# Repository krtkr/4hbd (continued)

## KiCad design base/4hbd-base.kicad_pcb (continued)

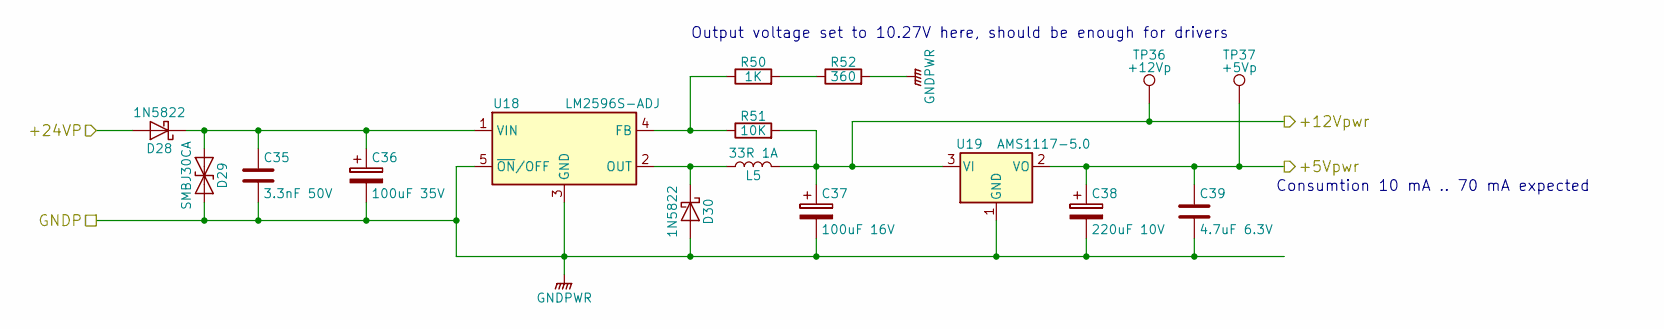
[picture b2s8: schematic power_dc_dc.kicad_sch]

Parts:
C35: 3.3nF 50V; C_0603_1608Metric
C36: 100uF 35V; CP_Elec_6.3x7.7
C37: 100uF 16V; CP_Elec_6.3x5.3
C38: 220uF 10V; CP_Elec_6.3x5.3
C39: 4.7uF 6.3V; C_0603_1608Metric
D28, D30: 1N5822; D_SMA
D29: SMBJ30CA; D_SMB
L5: 33R 1A; L_7.3x7.3_H3.5
R50: 1K; R_0603_1608Metric
R51: 10K; R_0603_1608Metric
R52: 360; R_0603_1608Metric
TP36: +12Vp; TestPoint_Pad_D1.5mm
TP37: +5Vp; TestPoint_Pad_D1.5mm
U18: LM2596S-ADJ; TO-263-5_TabPin3
U19: AMS1117-5.0; SOT-223

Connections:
/DIO/+12V: C37.1, L5.2, R51.2, TP36.1, U19.3 (VI); also elsewhere on the board
/MOSFETs/CurSense/Isolation/+5Vpwr: C38.1, C39.1, TP37.1, U19.2 (VO), U19.4; also elsewhere on the board
/Power DC/DC/+24VP: D28.2 (A); also elsewhere on the board
GNDPWR: C35.2, C36.2, C37.2, C38.2, C39.2, D29.2 (A2), D30.2 (A), R52.2, U18.3 (GND), U18.5 (~ON/OFF), U19.1 (GND); also elsewhere on the board
unnamed: C35.1, C36.1, D28.1 (K), D29.1 (A1), U18.1 (VIN)
unnamed: D30.1 (K), L5.1, U18.2 (OUT)
unnamed: R50.1, R51.1, U18.4 (FB)
unnamed: R50.2, R52.1

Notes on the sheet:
Output voltage set to 10.27V here, should be enough for drivers
Consumtion 10 mA .. 70 mA expected

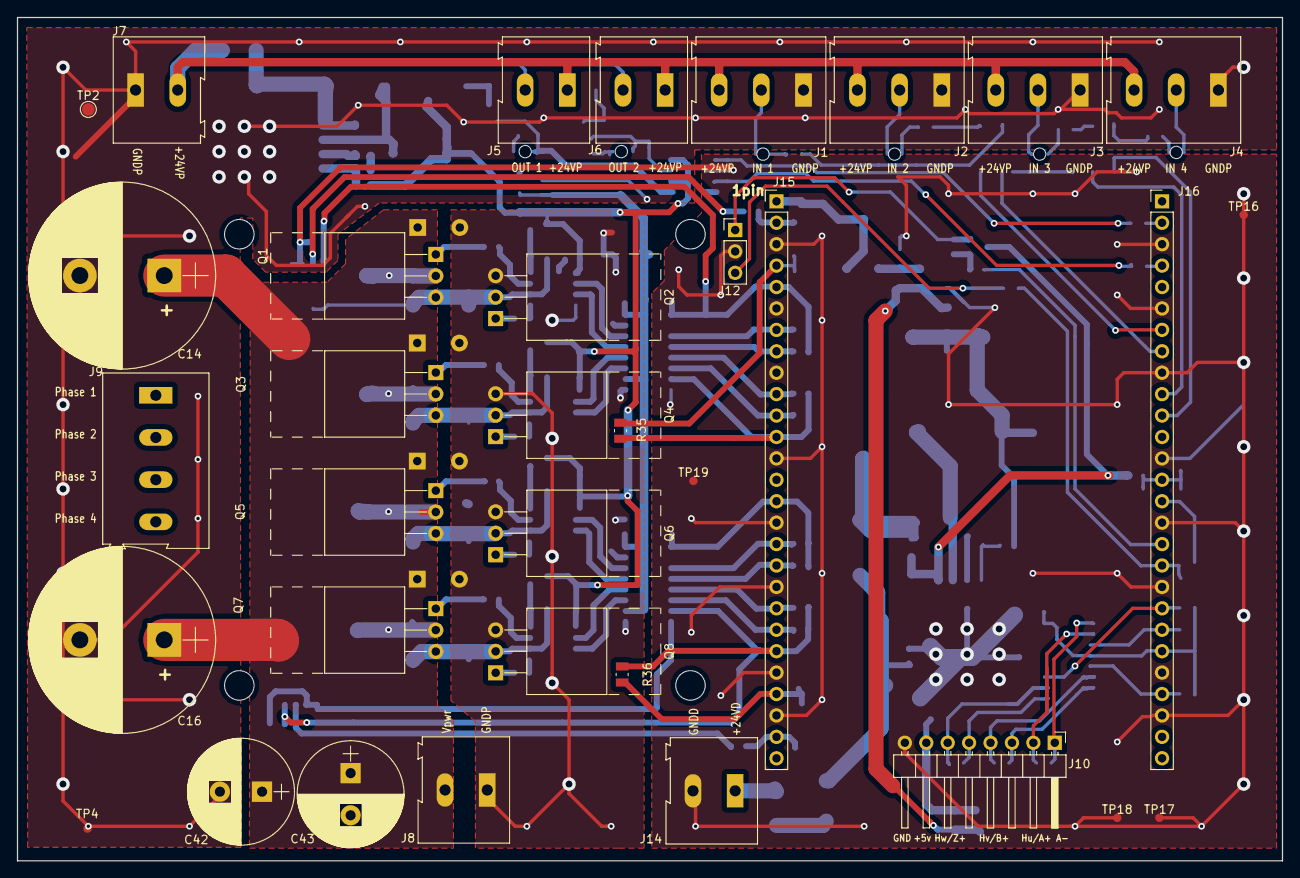
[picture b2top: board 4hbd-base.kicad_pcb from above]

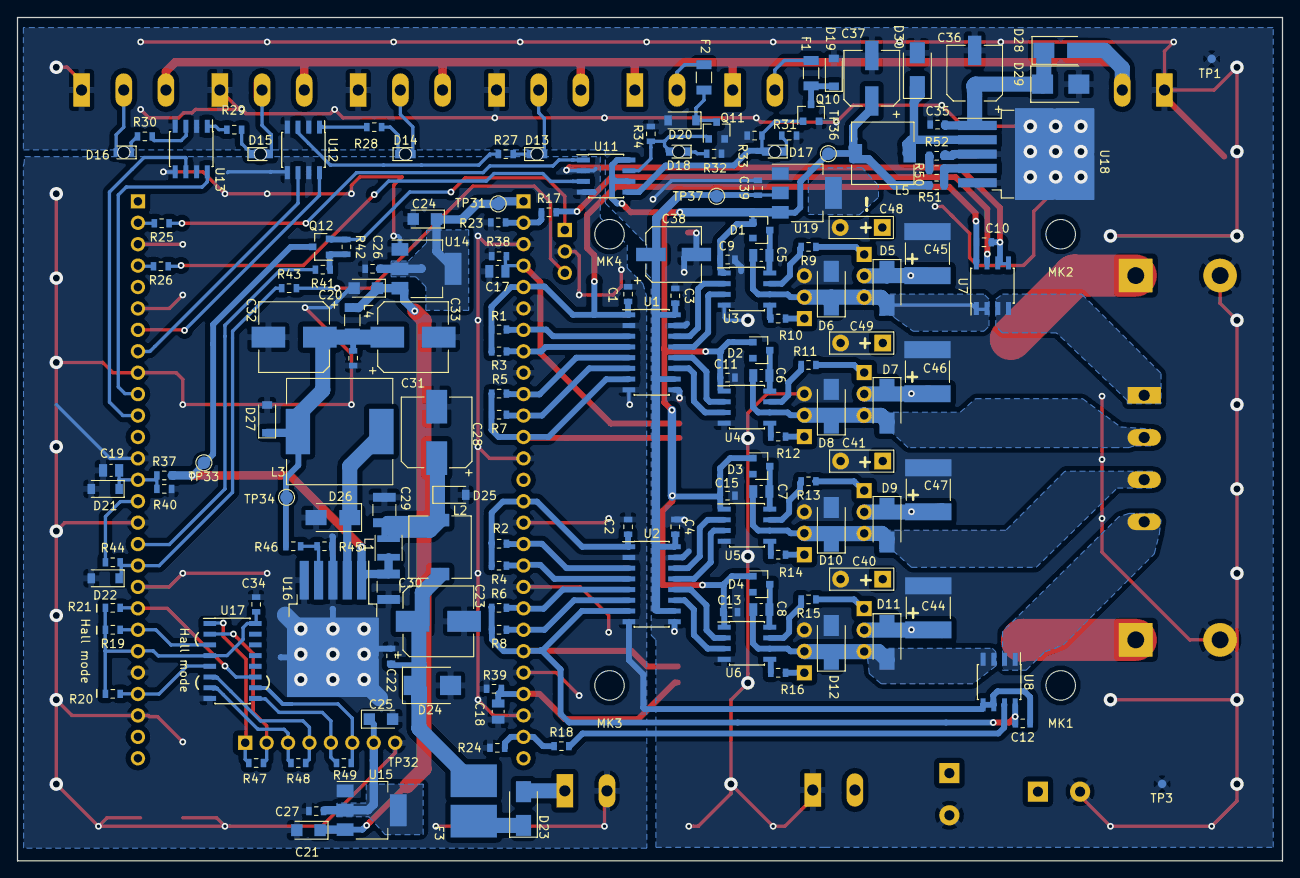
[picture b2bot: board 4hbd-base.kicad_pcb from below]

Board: 2 copper layers, 150.0 x 100.0 mm, 198 parts (164 on the bottom side), 113 nets.

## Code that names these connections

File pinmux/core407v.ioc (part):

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Mcu.Name=STM32F407V(E-G)Tx
Mcu.Package=LQFP100
Mcu.UserName=STM32F407VETx
PA0-WKUP.GPIOParameters=GPIO_Label
PA0-WKUP.GPIO_Label=ENC_A
PA0-WKUP.Signal=S_TIM2_CH1_ETR
PA1.GPIOParameters=GPIO_Label
PA1.GPIO_Label=ENC_B
PA1.Signal=S_TIM2_CH2
PA10.Mode=OTG/Dual_Role_Device
PA10.Signal=USB_OTG_FS_ID
PA11.Mode=OTG/Dual_Role_Device
PA11.Signal=USB_OTG_FS_DM
PA12.Mode=OTG/Dual_Role_Device
PA12.Signal=USB_OTG_FS_DP
PA13.Mode=JTAG_5_pins
PA13.Signal=SYS_JTMS-SWDIO
PA14.Mode=JTAG_5_pins
PA14.Signal=SYS_JTCK-SWCLK
PA15.Mode=JTAG_5_pins
PA15.Signal=SYS_JTDI
PA2.GPIOParameters=GPIO_Label
PA2.GPIO_Label=ENC_Z
PA2.Signal=GPIO_Input
PA4.Mode=NSS_Signal_Hard_Output
PA4.Signal=SPI1_NSS
PA5.Mode=Full_Duplex_Master
PA5.Signal=SPI1_SCK
PA6.Mode=Full_Duplex_Master
PA6.Signal=SPI1_MISO
PA7.Mode=Full_Duplex_Master
PA7.Signal=SPI1_MOSI
PA8.Mode=Activate_SOF_FS
PA8.Signal=USB_OTG_FS_SOF
PA9.Mode=Activate_VBUS
PA9.Signal=USB_OTG_FS_VBUS
PB1.Signal=ADCx_IN9
PB12.Mode=NSS_Signal_Hard_Output
PB12.Signal=SPI2_NSS
PB13.Mode=Full_Duplex_Master
PB13.Signal=SPI2_SCK
PB14.Mode=Full_Duplex_Master
PB14.Signal=SPI2_MISO
PB15.Mode=Full_Duplex_Master
PB15.Signal=SPI2_MOSI
PB3.Mode=JTAG_5_pins
PB3.Signal=SYS_JTDO-SWO
PB4.Mode=JTAG_5_pins
PB4.Signal=SYS_JTRST
PB5.GPIOParameters=GPIO_Label
PB5.GPIO_Label=USART1_DE
PB5.Signal=GPIO_Output
PB6.Mode=Asynchronous
PB6.Signal=USART1_TX
PB7.Mode=Asynchronous
PB7.Signal=USART1_RX
PB8.Mode=Master
PB8.Signal=CAN1_RX
PB9.Mode=Master
PB9.Signal=CAN1_TX
PC0.Signal=ADCx_IN10
PC14-OSC32_IN.Mode=LSE-External-Oscillator
PC14-OSC32_IN.Signal=RCC_OSC32_IN
PC15-OSC32_OUT.Mode=LSE-External-Oscillator
PC15-OSC32_OUT.Signal=RCC_OSC32_OUT
PC2.Signal=ADCx_IN12
PC4.Signal=ADCx_IN14
PC5.Signal=ADCx_IN15
PC6.GPIOParameters=GPIO_Label
PC6.GPIO_Label=FAN_PWM
PC6.Signal=S_TIM3_CH1
PD0.GPIOParameters=GPIO_Label
PD0.GPIO_Label=DI0
PD0.Signal=GPIO_Input
PD1.GPIOParameters=GPIO_Label
PD1.GPIO_Label=DI1
PD1.Signal=GPIO_Input
PD12.GPIOParameters=GPIO_Label
PD12.GPIO_Label=FAN_Pulse
PD12.Signal=S_TIM4_CH1
PD2.GPIOParameters=GPIO_Label
PD2.GPIO_Label=DI2
PD2.Signal=GPIO_Input
PD3.GPIOParameters=GPIO_Label
PD3.GPIO_Label=DI3
PD3.Signal=GPIO_Input
PD4.GPIOParameters=GPIO_Label
PD4.GPIO_Label=DO0
PD4.Signal=GPIO_Output
PD5.GPIOParameters=GPIO_Label
PD5.GPIO_Label=DO1
PD5.Signal=GPIO_Output
PE10.GPIOParameters=GPIO_Label
PE10.GPIO_Label=PWM1n
PE10.Mode=PWM Generation2 CH2 CH2N
PE10.Signal=TIM1_CH2N
PE11.GPIOParameters=GPIO_Label
PE11.GPIO_Label=PWM1p
PE11.Signal=S_TIM1_CH2
PE12.GPIOParameters=GPIO_Label
PE12.GPIO_Label=PWM2n
PE12.Mode=PWM Generation3 CH3 CH3N
PE12.Signal=TIM1_CH3N
PE13.GPIOParameters=GPIO_Label
PE13.GPIO_Label=PWM2p
PE13.Signal=S_TIM1_CH3
PE14.GPIOParameters=GPIO_Label
PE14.GPIO_Label=PWM3p
PE14.Signal=S_TIM1_CH4
PE15.GPIOParameters=GPIO_Label
PE15.GPIO_Label=PWM_Trip
PE15.Mode=Activate-Break-Input
PE15.Signal=TIM1_BKIN
PE7.GPIOParameters=GPIO_Label
PE7.GPIO_Label=PWM3n
PE7.Signal=GPIO_Output
PE8.GPIOParameters=GPIO_Label
PE8.GPIO_Label=PWM0n
PE8.Mode=PWM Generation1 CH1 CH1N
PE8.Signal=TIM1_CH1N
PE9.GPIOParameters=GPIO_Label
PE9.GPIO_Label=PWM0p
PE9.Signal=S_TIM1_CH1
PH0-OSC_IN.Mode=HSE-External-Oscillator
PH0-OSC_IN.Signal=RCC_OSC_IN
PH1-OSC_OUT.Mode=HSE-External-Oscillator
PH1-OSC_OUT.Signal=RCC_OSC_OUT
RCC.HSE_VALUE=8000000
RCC.SYSCLKFreq_VALUE=168000000
RCC.SYSCLKSource=RCC_SYSCLKSOURCE_PLLCLK

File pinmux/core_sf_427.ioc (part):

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Mcu.Name=STM32F427V(G-I)Tx
Mcu.Package=LQFP100
Mcu.UserName=STM32F427VGTx
PA0/WKUP.Signal=ADCx_IN0
PA1.Mode=RMII
PA1.Signal=ETH_REF_CLK
PA10.Signal=S_TIM1_CH3
PA11.Signal=S_TIM1_CH4
PA13.Mode=JTAG_5_pins
PA13.Signal=SYS_JTMS-SWDIO
PA14.Mode=JTAG_5_pins
PA14.Signal=SYS_JTCK-SWCLK
PA15.Mode=JTAG_5_pins
PA15.Signal=SYS_JTDI
PA2.Mode=RMII
PA2.Signal=ETH_MDIO
PA3.Signal=ADCx_IN3
PA4.Signal=ADCx_IN4
PA5.GPIOParameters=GPIO_Label
PA5.GPIO_Label=TIM1_CH2N
PA5.Signal=GPIO_Output
PA6.Mode=Activate-Break-Input
PA6.Signal=TIM1_BKIN
PA7.Mode=RMII
PA7.Signal=ETH_CRS_DV
PA8.Signal=S_TIM1_CH1
PA9.Signal=S_TIM1_CH2
PB0.GPIOParameters=GPIO_Label
PB0.GPIO_Label=TIM3_FAN_PWM
PB0.Signal=S_TIM3_CH3
PB1.Signal=ADCx_IN9
PB10.GPIOParameters=GPIO_Label
PB10.GPIO_Label=TIM2_FAN_PULSE
PB10.Signal=S_TIM2_CH3
PB11.Mode=RMII
PB11.Signal=ETH_TX_EN
PB12.Mode=RMII
PB12.Signal=ETH_TXD0
PB13.Mode=RMII
PB13.Signal=ETH_TXD1
PB14.GPIOParameters=GPIO_Label
PB14.GPIO_Label=USART3_DE
PB14.Signal=GPIO_Output
PB2/BOOT1.GPIOParameters=GPIO_Label
PB2/BOOT1.GPIO_Label=TIM1_CH1N
PB2/BOOT1.Signal=GPIO_Output
PB3.Mode=JTAG_5_pins
PB3.Signal=SYS_JTDO-SWO
PB4.Mode=JTAG_5_pins
PB4.Signal=SYS_JTRST
PB7.Signal=FMC_NL
PB8.Mode=Master
PB8.Signal=CAN1_RX
PB9.Mode=Master
PB9.Signal=CAN1_TX
PC0.Signal=ADCx_IN10
PC1.Mode=RMII
PC1.Signal=ETH_MDC
PC10.Mode=Asynchronous
PC10.Signal=USART3_TX
PC11.Mode=Asynchronous
PC11.Signal=USART3_RX
PC2.GPIOParameters=GPIO_Label
PC2.GPIO_Label=TIM1_CH4N
PC2.Signal=GPIO_Output
PC3.GPIOParameters=GPIO_Label
PC3.GPIO_Label=TIM1_CH3N
PC3.Signal=GPIO_Output
PC4.Mode=RMII
PC4.Signal=ETH_RXD0
PC5.Mode=RMII
PC5.Signal=ETH_RXD1
PD0.Mode=16b-da1
PD0.Signal=FMC_DA2
PD1.Mode=16b-da1
PD1.Signal=FMC_DA3
PD10.Mode=16b-da1
PD10.Signal=FMC_DA15
PD11.GPIOParameters=GPIO_Label
PD11.GPIO_Label=TIM4_ENC_Z
PD11.Signal=GPIO_Input
PD12.GPIOParameters=GPIO_Label
PD12.GPIO_Label=TIM4_ENC_A
PD12.Signal=S_TIM4_CH1
PD13.GPIOParameters=GPIO_Label
PD13.GPIO_Label=TIM4_ENC_B
PD13.Signal=S_TIM4_CH2
PD14.Mode=16b-da1
PD14.Signal=FMC_DA0
PD15.Mode=16b-da1
PD15.Signal=FMC_DA1
PD3.Mode=BurstReadWrite1
PD3.Signal=FMC_CLK
PD4.Mode=MuxedPsram1
PD4.Signal=FMC_NOE
PD5.Mode=MuxedPsram1
PD5.Signal=FMC_NWE
PD6.Mode=SynchronousWait1
PD6.Signal=FMC_NWAIT
PD7.Mode=NorPsramChipSelect1_1
PD7.Signal=FMC_NE1
PD8.Mode=16b-da1
PD8.Signal=FMC_DA13
PD9.Mode=16b-da1
PD9.Signal=FMC_DA14
PE0.Mode=2ByteEnable1
PE0.Signal=FMC_NBL0
PE1.Mode=2ByteEnable1
PE1.Signal=FMC_NBL1
PE10.Mode=16b-da1
PE10.Signal=FMC_DA7
PE11.Mode=16b-da1
PE11.Signal=FMC_DA8
PE12.Mode=16b-da1
PE12.Signal=FMC_DA9
PE13.Mode=16b-da1
PE13.Signal=FMC_DA10
PE14.Mode=16b-da1
PE14.Signal=FMC_DA11
PE15.Mode=16b-da1
PE15.Signal=FMC_DA12
PE7.Mode=16b-da1
PE7.Signal=FMC_DA4
PE8.Mode=16b-da1
PE8.Signal=FMC_DA5
PE9.Mode=16b-da1
PE9.Signal=FMC_DA6
PH0/OSC_IN.Mode=HSE-External-Clock-Source
PH0/OSC_IN.Signal=RCC_OSC_IN
PH1/OSC_OUT.Mode=HSE-External-Clock-Source
PH1/OSC_OUT.Signal=RCC_OSC_OUT
RCC.HSE_VALUE=8000000
RCC.SYSCLKFreq_VALUE=180000000
RCC.SYSCLKSource=RCC_SYSCLKSOURCE_PLLCLK

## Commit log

2017-11-27 Initial hierarchy of 4hbd base board.
2017-11-27 Two transistors was added to mosfets_sens_isol.sch
2017-11-28 1. krtkr/kicad-library was included
    2. mosfets_sens_isol.sch was edited
2017-11-29 Change path for lib krtkr/kicad-library
2017-11-29 fix 'R'
2017-11-29 1. Use submodules to track kicad-library used with project. 2. Use relative path for library search path.
2017-12-02 draft 0.01 of mosfets_sens_isol.sch
2017-12-04 draft 0.02 of mosfets_sens_isol.sch
2017-12-08 Add recent kicad footprints into repository.
2017-12-08 1. Update footprint library. 2. Link base project to the footprints library.
2017-12-08 Update library handling methodology: 1. We prefere project local settings for fooprints and symbols library setup. 2. Store links to library git hashes as submodules in project.
2017-12-08 update link to submodule
2017-12-09 1. Add STM32 pinmux for Core407V. 2. Add 'power' lib. 3. Add interface to Core407V board.
2017-12-09 Update pinmux: add oscillators.
2017-12-13 draft 0.03 of mosfets_sens_isol.sch
2017-12-13 draft 0.04 of mosfets_sens_isol.sch
2017-12-13 Add peripherals usage planning for STM32 MCUs.
2017-12-15 draf 0.1 of mosfets_sens_isol.sch
2017-12-16 kicad lib was updated
2017-12-19 Implement digital DC/DC convertor page.
2017-12-20 1. Separate dio_can_rs485 sheet into two: dio + can_rs485. 2. Move can and rs485 into digital power domain 3. Add CAN transiever to can_rs485 sheet
2017-12-22 Update pinmux: 1. Add DMA channels usage info into CubeMX 2. Use ADC2 and ADC3 for motor coils current monitoring
2017-12-22 Update schematics: 1. Connect analog voltages to MCU board connector 2. Implement Power DC/DC
2017-12-26 updated kikad-lib
2017-12-26 encoder.sch was modified
2017-12-27 dio.sch was updated
2017-12-28 Update base board: 1. Add extra analog voltage input to core board. -> update pinmux 2. Assign most footprints. 3. Generate netlist. 4. Add core_sf board. 5. Add kicad_symbols library submodule.
2017-12-28 temp-sens-fan was created
2017-12-28 Update footprints.
2017-12-28 some test points
2017-12-28 A few updates to test points.
2018-01-02 symbols and footprints for KF141R
2018-01-02 update to spring terminal 2.54 KF141R
2018-01-02 annotate sch
2018-01-02 added footprints, created netlist
2018-01-02 assign footprints
2018-01-02 mount hole was added
2018-01-04 mount hole
2018-01-05 fix for pcb
2018-01-05 define board outline
2018-01-05 update submodule from krtkr
2018-01-05 update pcb for TerminalBlock_KaiFeng footprint lib
2018-01-05 update pcb
2018-01-06 kicad footprints was updated
2018-01-06 fix in kikad FP
2018-01-06 update fooprints for mosfet
2018-01-07 pcb was edited
2018-02-12 current pcb
2018-02-21 upd adc
2018-02-28 Possible core sf board layout.
2018-03-01 upd kicad-lib
2018-03-08 update core pinout
2018-03-12 current version
2018-03-12 current v 4hbd
2018-03-12 Connect GND pad to plane of U17 directly without thermal relief.
2018-03-12 add power vias
2018-03-12 generate gerber files
2018-03-12 update gerbers
2018-03-13 fix vias lost netname by traces
2018-03-13 update poligone
2018-03-13 update gerber
2018-03-13 one more update gerber
2018-03-13 this revision was sent to factory rezonit
2018-04-07 repair link to submodule kicad-footprints
2018-04-07 new link to submodule kikad-footprints
2018-04-09 edit reference for diodes in digital_dc_dc
2018-04-21 debug design
2018-04-22 debug core was prepared to rezonit
2022-05-02 migration to kicad 6
